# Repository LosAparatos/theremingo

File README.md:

# Theremingo

A handmade analog electromagnetic theremin, designed and built by [Los Aparatos](https://losaparatos.com.ar) in Tucumán, Argentina.

## What is it?

Theremingo is an analog theremin — a touchless electronic instrument played by moving your hands near its antennas, which affect pitch and volume through electromagnetic field disturbance. No microcontroller, no code: fully analog circuitry.

## Repository contents

- `/schematics` — circuit design files, created in **EagleCAD (v9.0)**. You'll need Eagle (or a compatible tool like KiCad with an Eagle import plugin) to open the native files.
- `/images` — photos of the finished instrument, including its final enclosure — a deer-shaped antenna cut as an SVG, not included among the schematic files.

## About Los Aparatos

Los Aparatos is an electronic design studio building experimental musical instruments — synthesizers, sound toys and DIY kits — handmade in Tucumán, Argentina, since 2007.

Other instruments: [Auduina](https://gitlab.com/los-aparatos/auduina) (granular synth), Drawdio (a sound pencil that turns drawing into sound), CoyuyoC (a drone synth).

## Where to buy

[losaparatos.com.ar](https://losaparatos.com.ar) · [Tindie](https://www.tindie.com/stores/mateoaparato/) · [Etsy](https://losaparatos.etsy.com) · [Reverb](https://reverb.com/shop/los-aparatos)

## License

[CC BY-NC-SA 4.0](https://creativecommons.org/licenses/by-nc-sa/4.0/)

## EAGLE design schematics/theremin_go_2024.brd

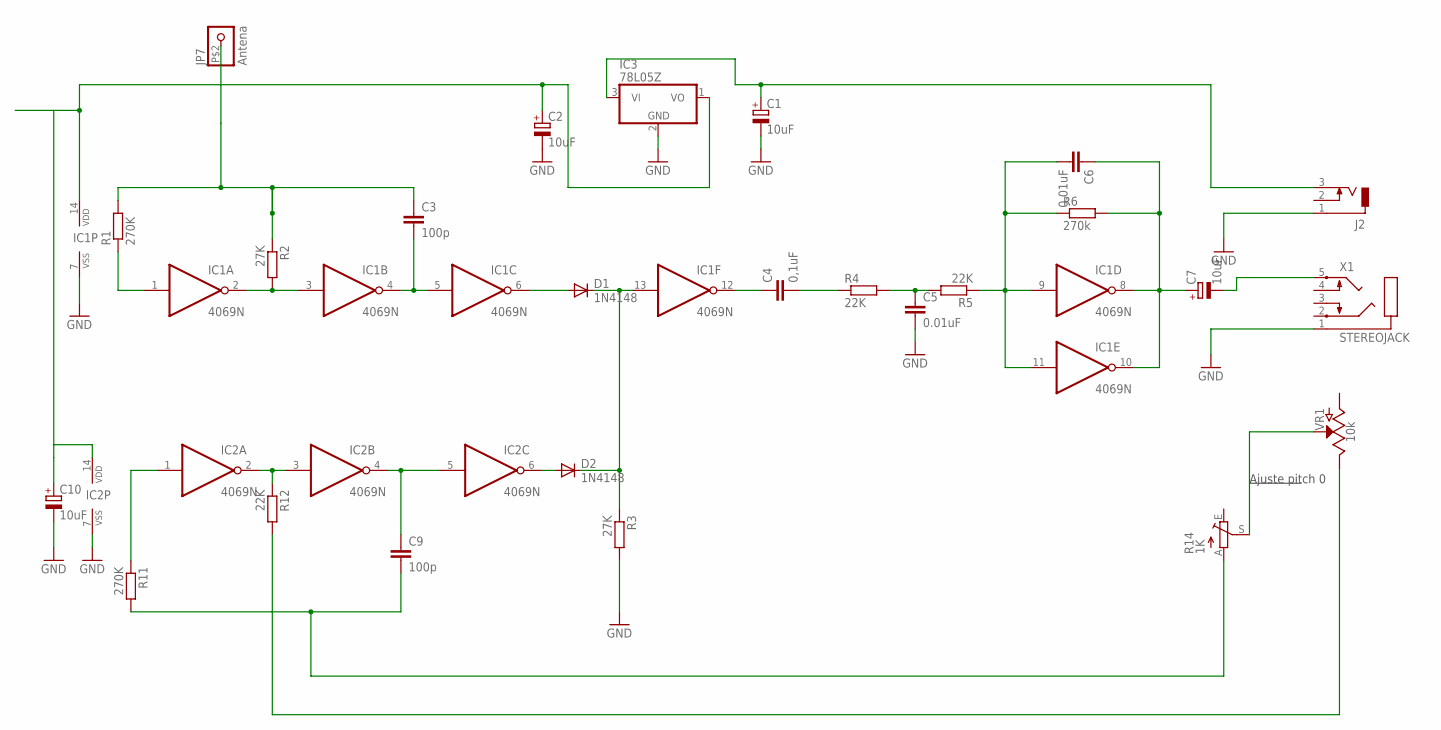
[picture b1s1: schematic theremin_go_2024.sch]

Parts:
C1, C2, C7, C10: 10uF; E2,5-6E
C3, C9: 100p; C050-030X075
C4: 0,1uF; C050-030X075
C5, C6: 0.01uF; C050-030X075
D1, D2: 1N4148; DO35-7
IC1, IC2: 4069N; DIL14
IC3: 78L05Z; TO92
J2: DCJ0303
JP7: Antena; 1X01
R1, R11: 270K; 0309/10
R2, R3: 27K; 0309/10
R4, R5, R12: 22K; 0309/10
R6: 270k; 0309/10
R14: 1K; S64W
VR1: 10k; POT-PTH-ALPS
X1: STEREOJACK; STX3100

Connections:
GND: C1.-, C2.-, C5.2, C10.-, IC1.7 (VSS), IC2.7 (VSS), IC3.2 (GND), J2.1, R3.2, X1.1
unnamed: C2.+, C10.+, IC1.14 (VDD), IC2.14 (VDD), IC3.1 (VO)
unnamed: C1.+, IC3.3 (VI), J2.3
unnamed: IC1.1 (I), R1.1
unnamed: C3.1, JP7.P$2, R1.2, R2.1
unnamed: IC1.2 (O), IC1.3 (I), R2.2
unnamed: C3.2, IC1.4 (O), IC1.5 (I)
unnamed: D1.A, IC1.6 (O)
unnamed: D1.C, D2.C, IC1.13 (I), R3.1
unnamed: C4.1, IC1.12 (O)
unnamed: C4.2, R4.1
unnamed: C9.2, R11.2, R14.A
unnamed: R14.S, VR1.P$2 (S)
unnamed: C6.2, IC1.9 (I), IC1.11 (I), R5.1, R6.1
unnamed: IC2.1 (I), R11.1
unnamed: C9.1, IC2.4 (O), IC2.5 (I)
unnamed: D2.A, IC2.6 (O)
unnamed: IC2.2 (O), IC2.3 (I), R12.1
unnamed: C6.1, C7.+, IC1.8 (O), IC1.10 (O), R6.2
unnamed: C7.-, X1.5
unnamed: R12.2, VR1.P$1 (E)
unnamed: C5.1, R4.2, R5.2

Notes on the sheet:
Ajuste pitch 0

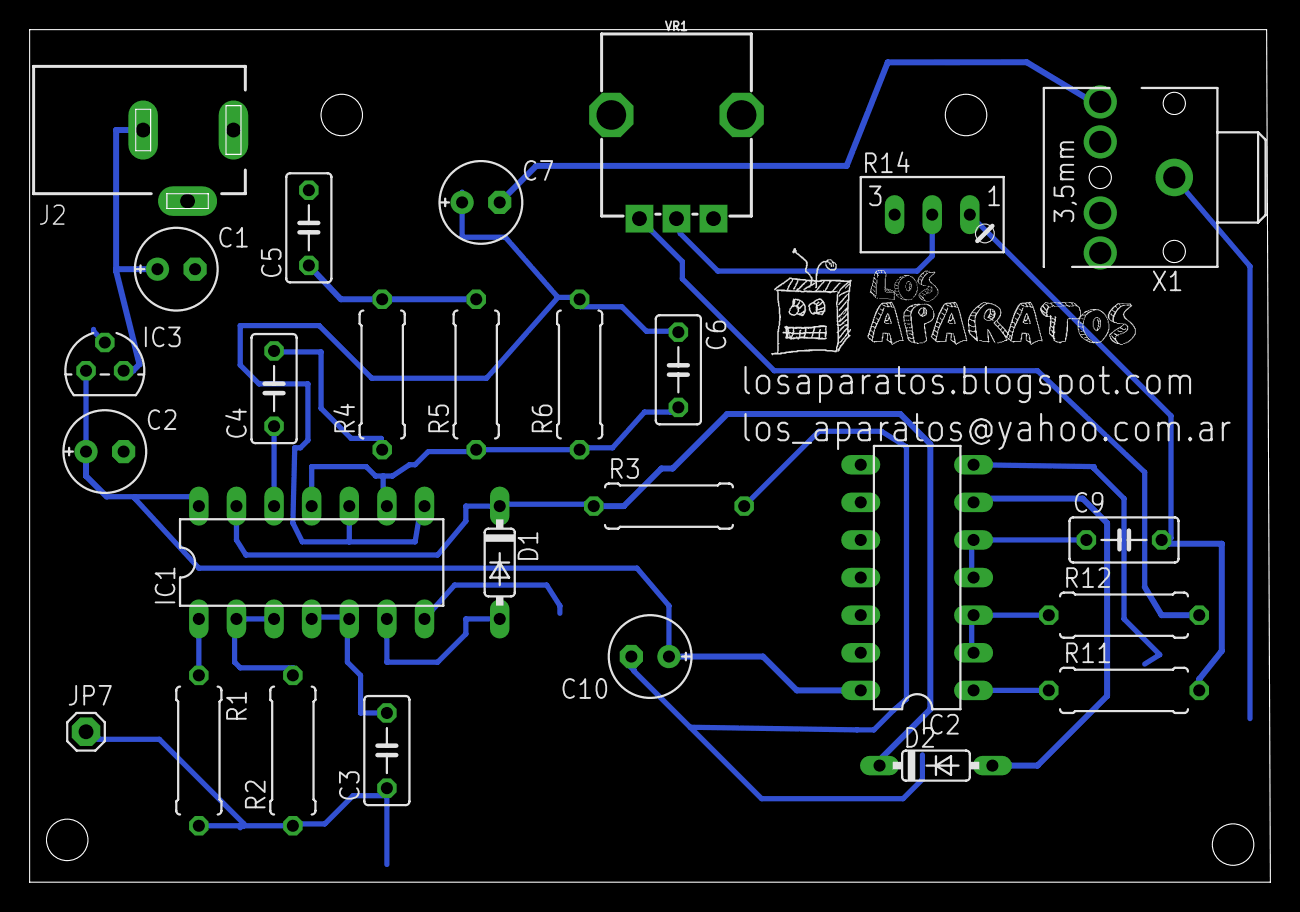
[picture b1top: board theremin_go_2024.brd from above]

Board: 2 copper layers, 83.8 x 57.6 mm, 27 parts (0 on the bottom side), 22 nets.

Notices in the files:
parts and their libraries:
SparkFun-Resistors: Licensing: Creative Commons ShareAlike 4.0 International - https://creativecommons.org/licenses/by-sa/4.0
